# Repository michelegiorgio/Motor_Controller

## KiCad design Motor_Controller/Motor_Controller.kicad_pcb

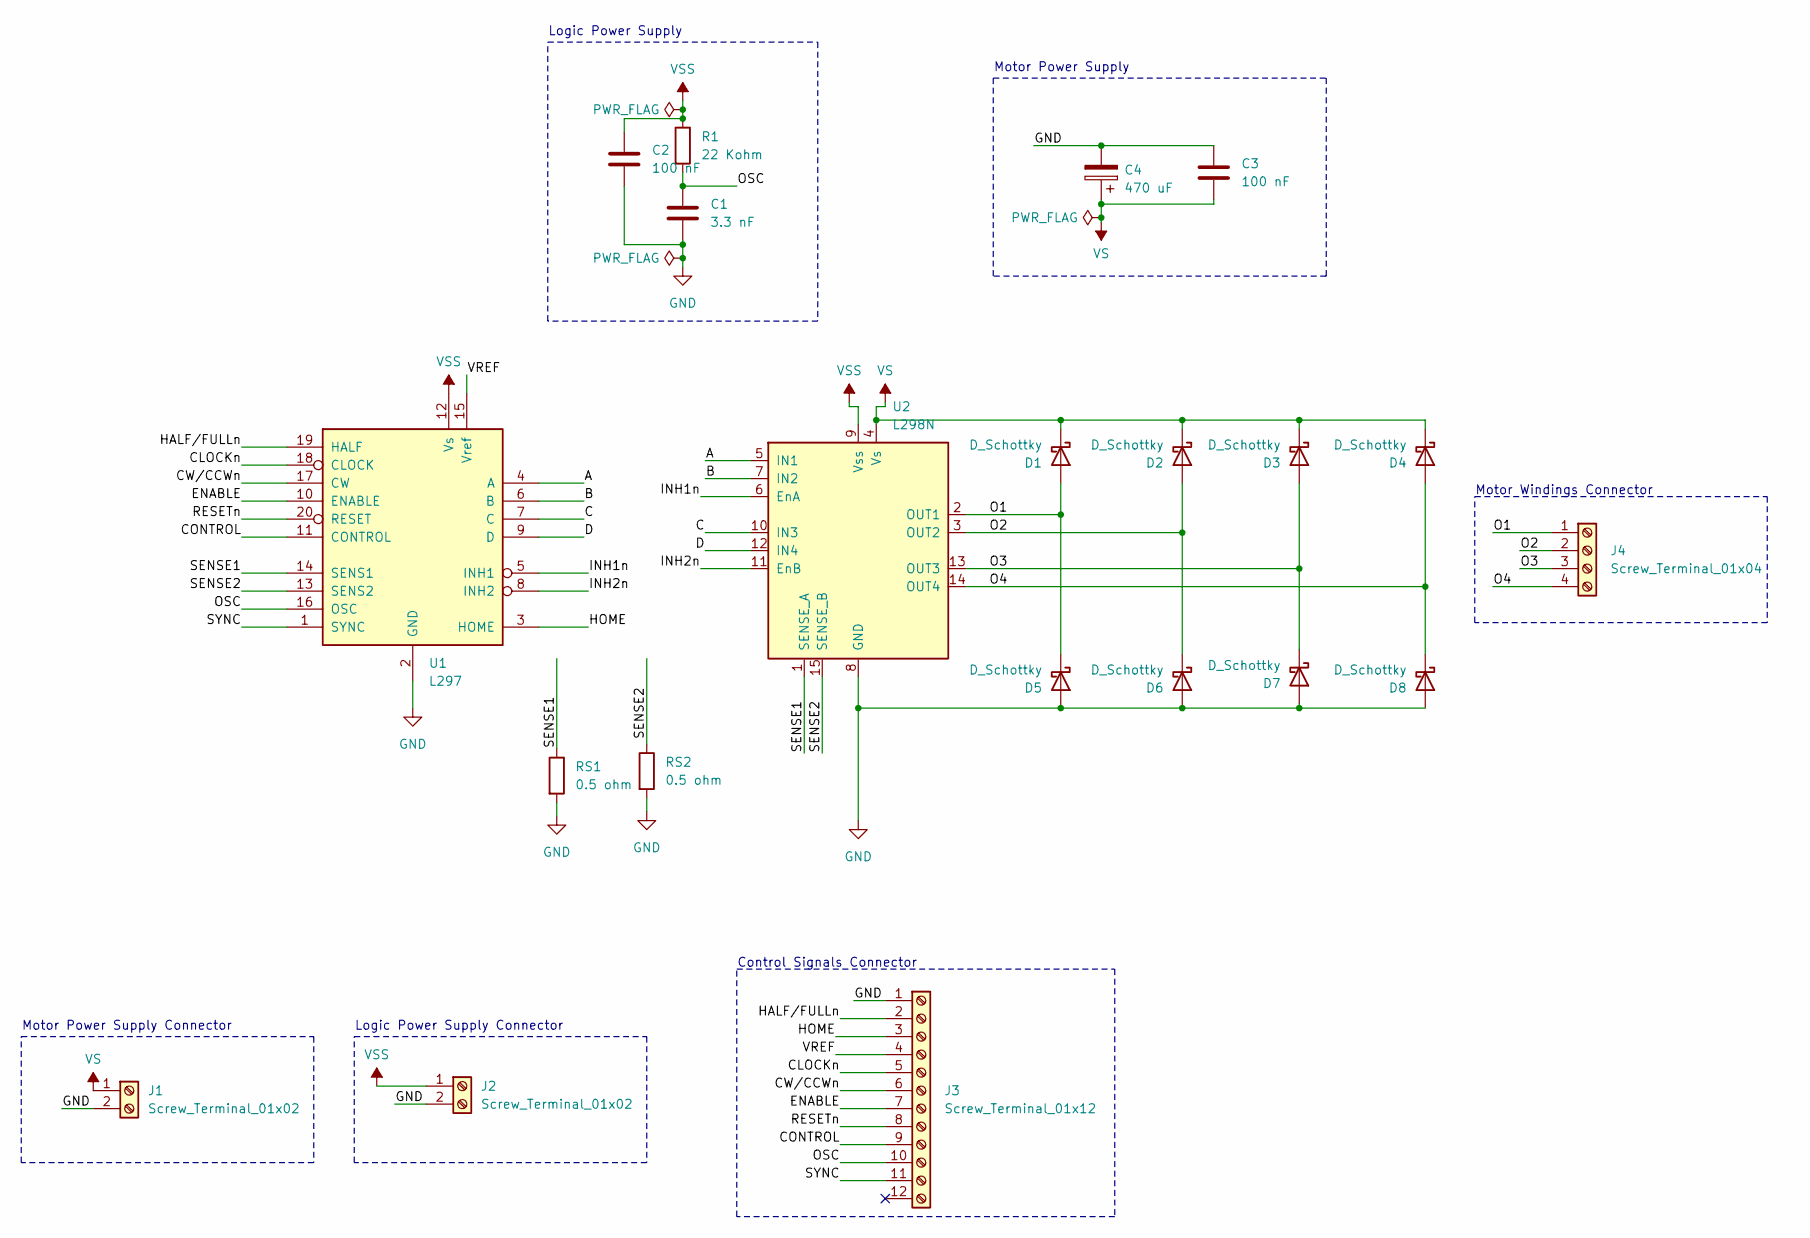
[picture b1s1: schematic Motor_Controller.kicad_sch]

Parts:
C1: 3.3 nF; C_Rect_L10.0mm_W3.0mm_P7.50mm_FKS3_FKP3
C2, C3: 100 nF; C_Rect_L7.5mm_W6.5mm_P5.00mm
C4: 470 uF; CP_Radial_D13.0mm_P5.00mm
D1, D2, D3, D4, D5, D6, D7, D8: D_Schottky; D_DO-27_P15.24mm_Horizontal
J1, J2: Screw_Terminal_01x02; TerminalBlock_Phoenix_MKDS-1,5-2-5.08_1x02_P5.08mm_Horizont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
J3: Screw_Terminal_01x12; TerminalBlock_Phoenix_MKDS-1,5-12-5.08_1x12_P5.08mm_Horizon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
J4: Screw_Terminal_01x04; TerminalBlock_Phoenix_MKDS-1,5-4-5.08_1x04_P5.08mm_Horizont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
R1: 22 Kohm; R_Axial_DIN0922_L20.0mm_D9.0mm_P25.40mm_Horizontal
RS1, RS2: 0.5 ohm; R_Axial_DIN0414_L11.9mm_D4.5mm_P15.24mm_Horizontal
U1: L297
U2: L298N; TO-220-15_P2.54x2.54mm_StaggerOdd_Lead4.58mm_Vertical

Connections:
/A: U1.4 (A), U2.5 (IN1)
/B: U1.6 (B), U2.7 (IN2)
/C: U1.7 (C), U2.10 (IN3)
/CLOCKn: J3.5, U1.18 (CLOCK)
/CONTROL: J3.9, U1.11 (CONTROL)
/CW/CCWn: J3.6, U1.17 (CW)
/D: U1.9 (D), U2.12 (IN4)
/ENABLE: J3.7, U1.10 (ENABLE)
/HALF/FULLn: J3.2, U1.19 (HALF)
/HOME: J3.3, U1.3 (HOME)
/INH1n: U1.5 (INH1), U2.6 (EnA)
/INH2n: U1.8 (INH2), U2.11 (EnB)
/O1: D1.2 (A), D5.1 (K), J4.1, U2.2 (OUT1)
/O2: D2.2 (A), D6.1 (K), J4.2, U2.3 (OUT2)
/O3: D3.2 (A), D7.1 (K), J4.3, U2.13 (OUT3)
/O4: D4.2 (A), D8.1 (K), J4.4, U2.14 (OUT4)
/OSC: C1.1, J3.10, R1.2, U1.16 (OSC)
/RESETn: J3.8, U1.20 (RESET)
/SENSE1: RS1.1, U1.14 (SENS1), U2.1 (SENSE_A)
/SENSE2: RS2.1, U1.13 (SENS2), U2.15 (SENSE_B)
/SYNC: J3.11, U1.1 (SYNC)
/VREF: J3.4, U1.15 (Vref)
GND: C1.2, C2.2, C3.1, C4.2, D5.2 (A), D6.2 (A), D7.2 (A), D8.2 (A), J1.2, J2.2, J3.1, RS1.2, RS2.2, U1.2 (GND), U2.8 (GND)
VS: C3.2, C4.1, D1.1 (K), D2.1 (K), D3.1 (K), D4.1 (K), J1.1, U2.4 (Vs)
VSS: C2.1, J2.1, R1.1, U1.12 (Vs), U2.9 (Vss)

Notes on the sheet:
Logic Power Supply Connector
Motor Power Supply
Logic Power Supply
Control Signals Connector
Motor Power Supply Connector
Motor Windings Connector

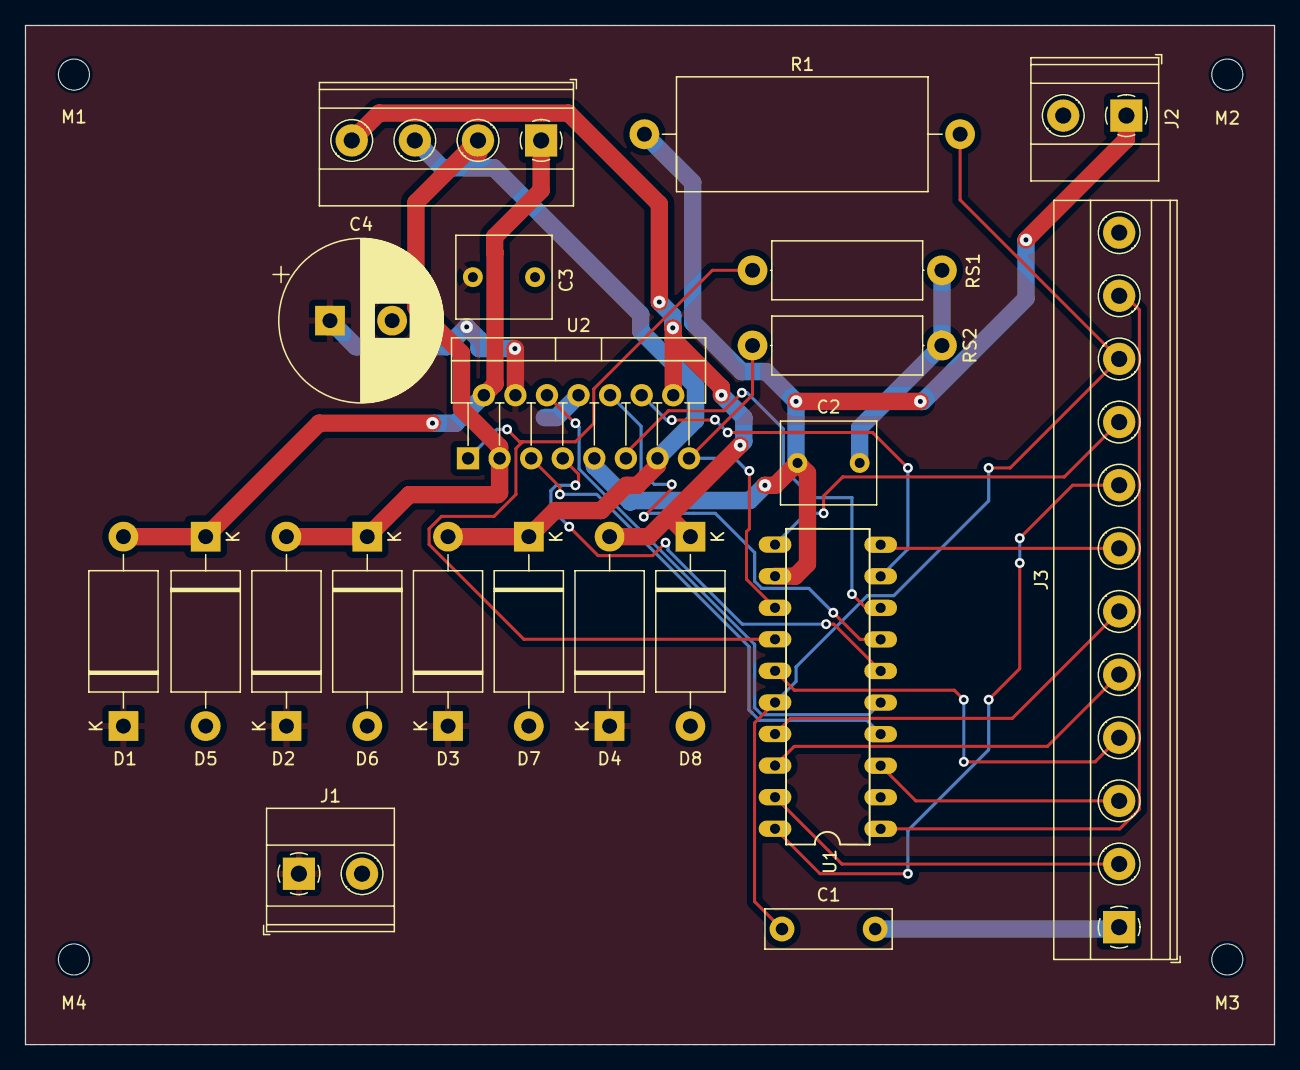
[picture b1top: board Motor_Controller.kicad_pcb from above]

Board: 2 copper layers, 100.5 x 82.0 mm, 25 parts (0 on the bottom side), 25 nets.

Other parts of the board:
M1, M2, M3, M4: MountingHole_2.5mm

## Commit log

2024-07-05 Motor_Controller Project
